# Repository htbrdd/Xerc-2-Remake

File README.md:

# Xerc-2-Remake
Xbox Xerc 2 Remake

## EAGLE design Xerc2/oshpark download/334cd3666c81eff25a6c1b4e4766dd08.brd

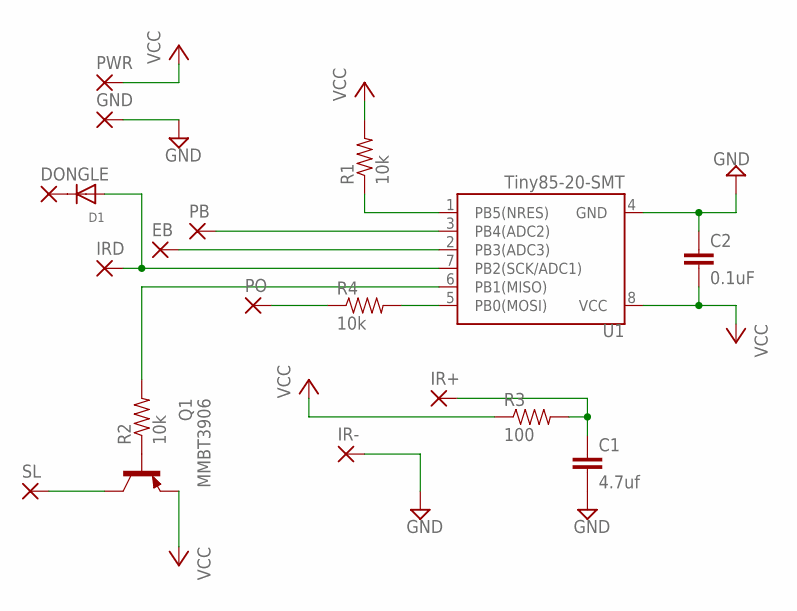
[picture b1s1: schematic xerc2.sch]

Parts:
C1: 4.7uf; 0603-CAP
C2: 0.1uF; 0603-CAP
D1: DIODESOD-323F; SOD-323F
DONGLE: SMD5; SMD2,54-5,08
EB: SMD5; SMD2,54-5,08
GND: SMD5; SMD2,54-5,08
IR+: SMD5; SMD2,54-5,08
IR-: SMD5; SMD2,54-5,08
IRD: SMD5; SMD2,54-5,08
MMBT3906: Q1; SOT23
PB: SMD5; SMD2,54-5,08
PO: SMD5; SMD2,54-5,08
PWR: SMD5; SMD2,54-5,08
R1, R2, R4: 10k; 0603-RES
R3: 100; 0603-RES
SL: SMD5; SMD2,54-5,08
U1: Tiny85-20-SMT; SO08-EIAJ

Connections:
GND: C1.2, C2.1, GND.1, IR-.1, U1.4 (GND)
unnamed: PB.1, U1.3 (PB4(ADC2))
unnamed 2: R1.1, U1.1 (PB5(NRES)); also elsewhere on the board
unnamed: EB.1, U1.2 (PB3(ADC3))
unnamed 4: D1.A, IRD.1, U1.7 (PB2(SCK/ADC1)); also elsewhere on the board
unnamed 5: R2.2, U1.6 (PB1(MISO)); also elsewhere on the board
unnamed: MMBT3906.1 (B), R2.1
unnamed: MMBT3906.3 (C), SL.1
unnamed: C1.1, IR+.1, R3.2
unnamed 9: R4.2, U1.5 (PB0(MOSI)); also elsewhere on the board
unnamed: PO.1, R4.1
unnamed: D1.C, DONGLE.1
VCC: C2.2, MMBT3906.2 (E), PWR.1, R1.2, R3.1, U1.8 (VCC); also elsewhere on the board

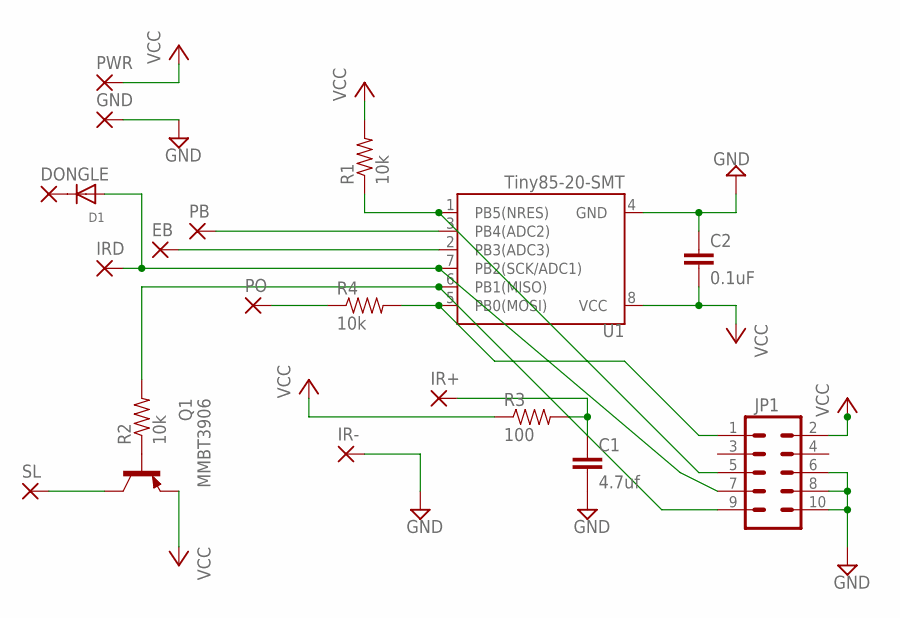
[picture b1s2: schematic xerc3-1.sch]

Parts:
C1: 4.7uf; 0603-CAP
C2: 0.1uF; 0603-CAP
D1: DIODESOD-323F; SOD-323F
DONGLE: SMD5; SMD2,54-5,08
EB: SMD5; SMD2,54-5,08
GND: SMD5; SMD2,54-5,08
IR+: SMD5; SMD2,54-5,08
IR-: SMD5; SMD2,54-5,08
IRD: SMD5; SMD2,54-5,08
JP1: M05X2SHD; 2X5-SHROUDED
MMBT3906: Q1; SOT23
PB: SMD5; SMD2,54-5,08
PO: SMD5; SMD2,54-5,08
PWR: SMD5; SMD2,54-5,08
R1, R2, R4: 10k; 0603-RES
R3: 100; 0603-RES
SL: SMD5; SMD2,54-5,08
U1: Tiny85-20-SMT; SO08-EIAJ

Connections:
GND: C1.2, C2.1, GND.1, IR-.1, U1.4 (GND)
unnamed: PB.1, U1.3 (PB4(ADC2))
unnamed: JP1.5, R1.1, U1.1 (PB5(NRES))
unnamed: EB.1, U1.2 (PB3(ADC3))
unnamed: D1.A, IRD.1, JP1.7, U1.7 (PB2(SCK/ADC1))
unnamed: JP1.9, R2.2, U1.6 (PB1(MISO))
unnamed: MMBT3906.1 (B), R2.1
unnamed: MMBT3906.3 (C), SL.1
unnamed: C1.1, IR+.1, R3.2
unnamed: JP1.1, R4.2, U1.5 (PB0(MOSI))
unnamed: PO.1, R4.1
unnamed: D1.C, DONGLE.1
unnamed: JP1.6, JP1.8, JP1.10
VCC: C2.2, JP1.2, MMBT3906.2 (E), PWR.1, R1.2, R3.1, U1.8 (VCC)

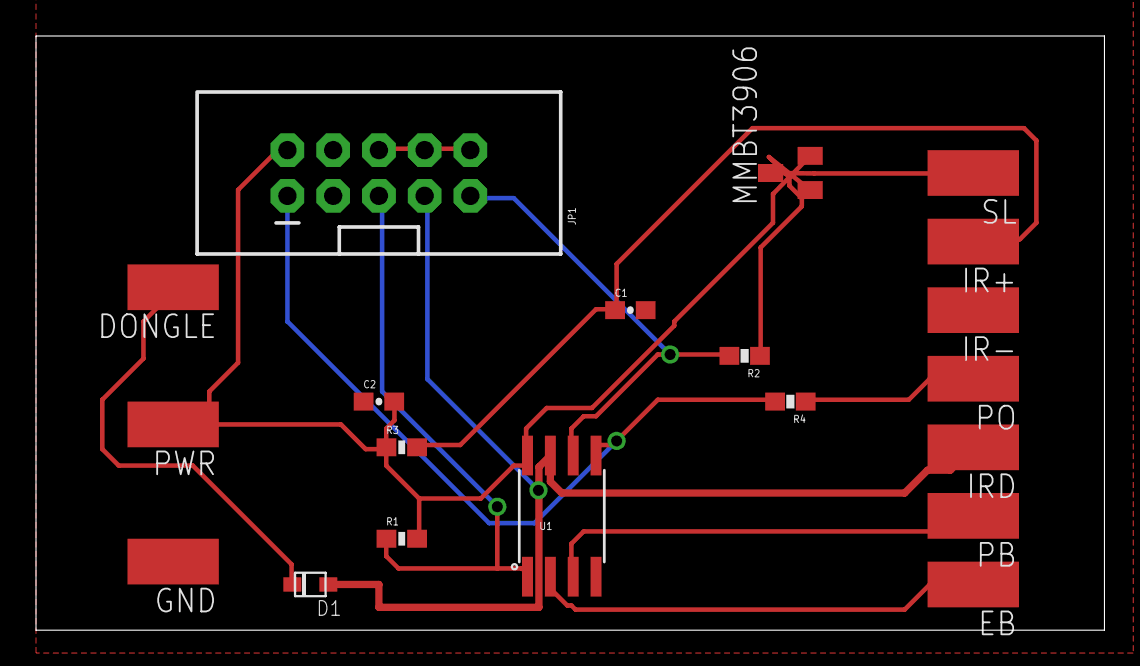
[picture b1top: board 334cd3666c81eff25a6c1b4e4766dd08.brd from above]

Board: 2 copper layers, 59.4 x 33.0 mm, 20 parts (0 on the bottom side), 14 nets.

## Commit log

2017-04-23 Board files
2017-04-23 added user manual and hex files
2017-04-23 added more diagrams and pictures
2017-04-24 added icsp header to board
2017-05-06 bom lists
2017-05-06 lock file removed

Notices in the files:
parts and their libraries:
SparkFun-Capacitors: Licensing: Creative Commons ShareAlike 4.0 International - https://creativecommons.org/licenses/by-sa/4.0
